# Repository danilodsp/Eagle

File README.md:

# Eagle

## Description

Some PCB projects using Eagle

## Directories

- PIC

PIC programmer PCB for development (designed in 2010).

- fonteReg

Controlled voltage source.

- fonte

Simple voltage source.

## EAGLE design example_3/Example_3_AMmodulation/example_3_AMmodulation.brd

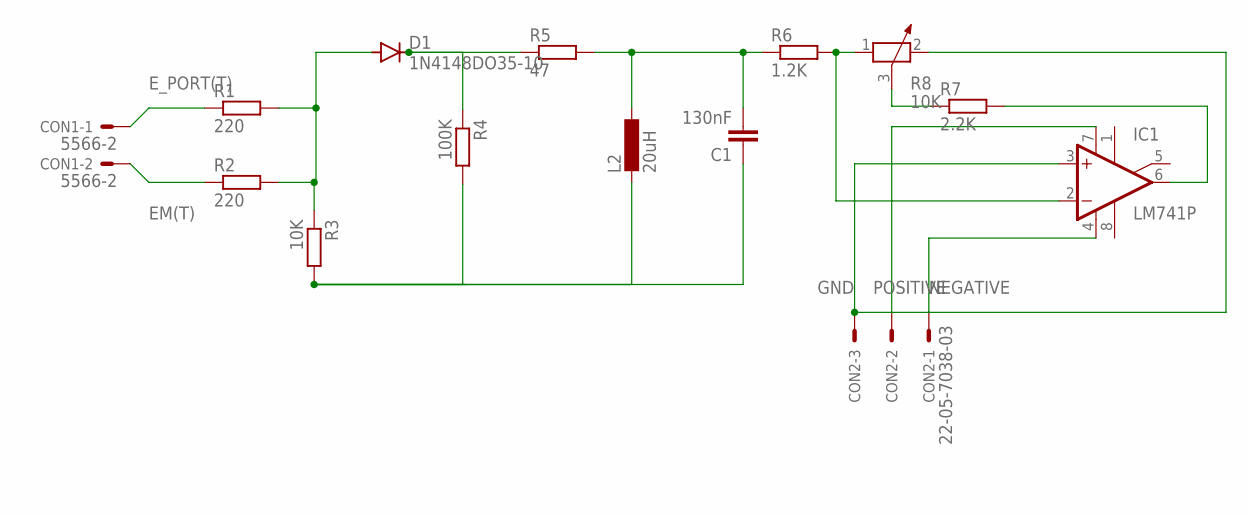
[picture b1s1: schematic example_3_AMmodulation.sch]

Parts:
C1: 130nF; C025-025X050
CON1: 5566-2
CON2: 22-05-7038-03; 7395-03
D1: 1N4148DO35-10; DO35-10
IC1: LM741P; DIL08
L2: 20uH; 0204/7
R1, R2: 220; 0204/7
R3: 10K; 0204/7
R4: 100K; 0204/7
R5: 47; 0204/7
R6: 1.2K; 0204/7
R7: 2.2K; 0204/7
R8: 10K; PT-10

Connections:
EM(T): CON1.2, R2.1
E_PORT(T): CON1.1, R1.1
GND: CON2.3, IC1.3 (+IN), R8.2
unnamed: D1.A, R1.2, R2.2, R3.1
unnamed: IC1.2 (-IN), R6.2, R8.1
unnamed: D1.C, R4.1, R5.1
unnamed: C1.2, L2.1, R5.2, R6.1
unnamed: R7.1, R8.3
unnamed: C1.1, L2.2, R3.2, R4.2
unnamed: IC1.6 (OUT), R7.2
NEGATIVE: CON2.1, IC1.4 (V-)
POSITIVE: CON2.2, IC1.7 (V+)

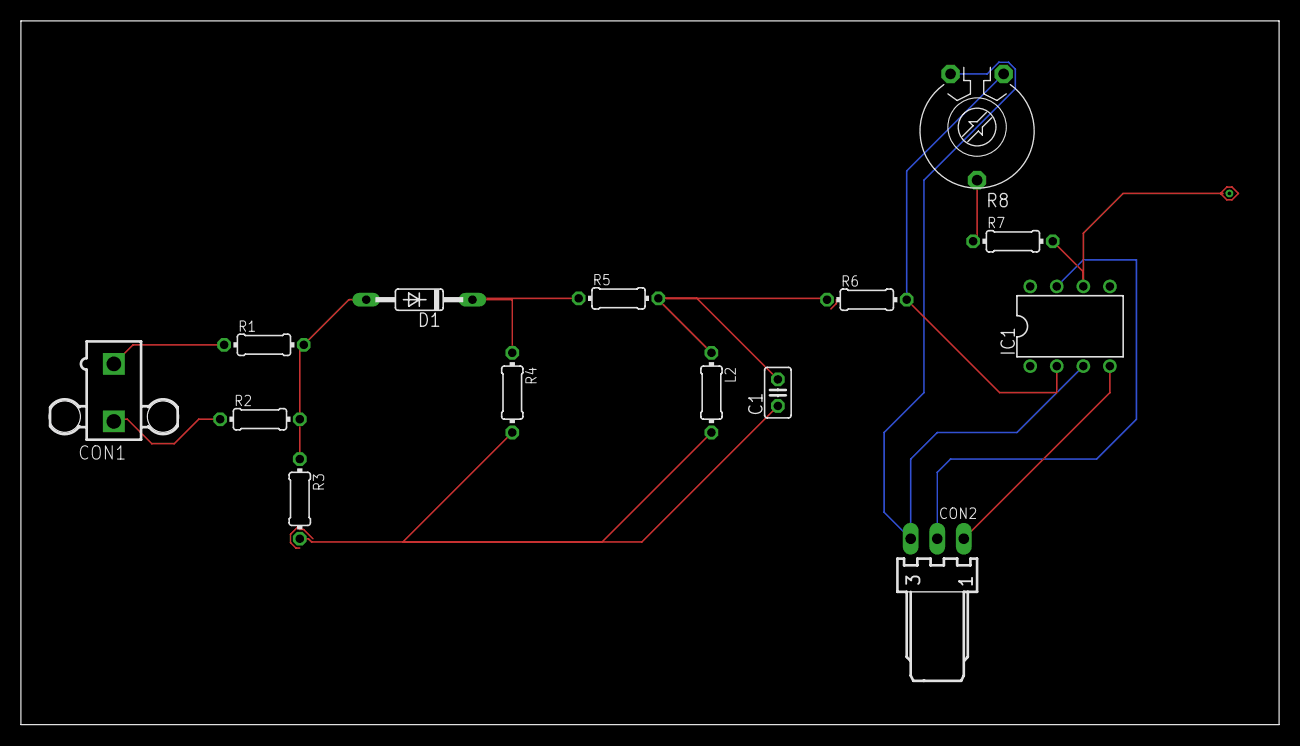
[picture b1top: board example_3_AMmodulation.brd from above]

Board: 2 copper layers, 120.3 x 67.3 mm, 14 parts (0 on the bottom side), 12 nets.

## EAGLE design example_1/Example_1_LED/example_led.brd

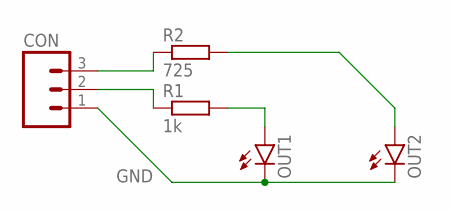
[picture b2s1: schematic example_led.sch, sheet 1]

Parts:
CON: M03; 03P
OUT1, OUT2: LED5MM
R1: 1k; 0204/7
R2: 725; 0204/7

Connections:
GND: CON.1, OUT1.K (C), OUT2.K (C)
unnamed: CON.3, R2.1
unnamed: OUT2.A, R2.2
unnamed: CON.2, R1.1
unnamed: OUT1.A, R1.2

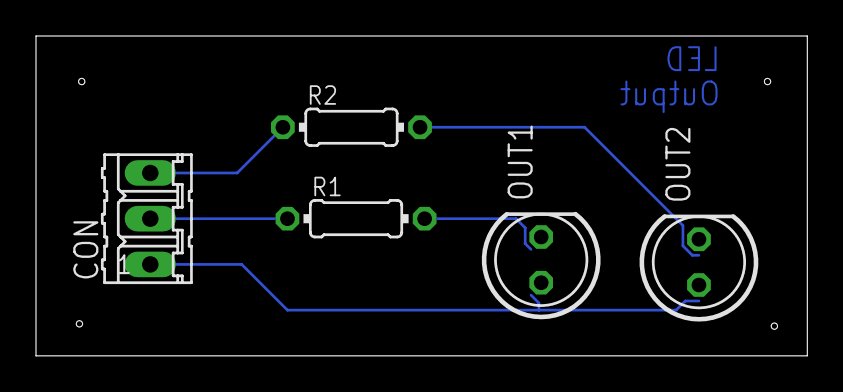
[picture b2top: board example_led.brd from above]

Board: 2 copper layers, 42.9 x 17.8 mm, 5 parts (0 on the bottom side), 5 nets.

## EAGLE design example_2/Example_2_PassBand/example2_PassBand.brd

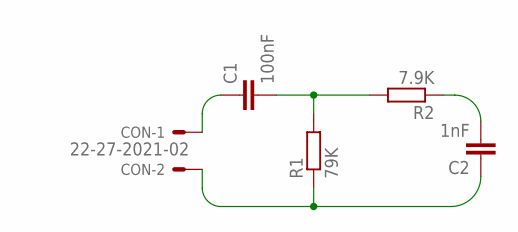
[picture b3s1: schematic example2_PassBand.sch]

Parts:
C1: 100nF; C5B2.5
C2: 1nF; C5B2.5
CON: 22-27-2021-02; 6410-02
R1: 79K; 0204/7
R2: 7.9K; 0204/7

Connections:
unnamed: C1.1, CON.1
unnamed: C1.2, R1.2, R2.2
unnamed: C2.2, R2.1
unnamed: C2.1, CON.2, R1.1

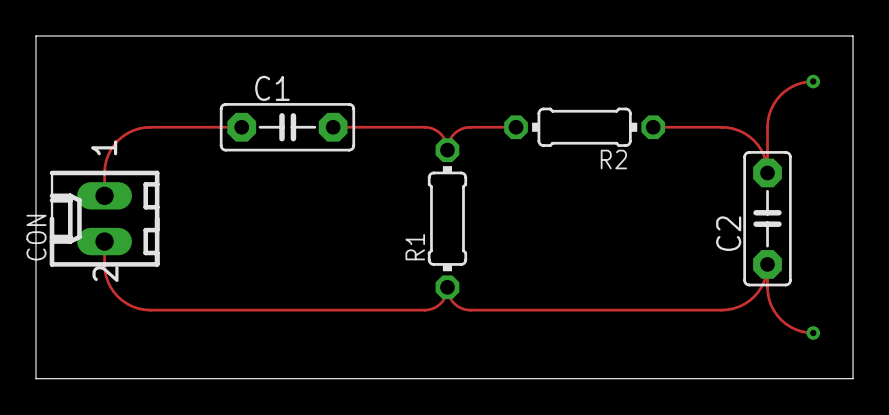
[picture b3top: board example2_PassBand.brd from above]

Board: 2 copper layers, 45.4 x 19.0 mm, 5 parts (0 on the bottom side), 4 nets.

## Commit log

2019-08-17 Added PIC programmer
2019-08-17 Updated the README
2019-08-17 Added a controlled source PCB
2019-08-17 Simple voltage source
2019-08-19 Add files via upload
    example_1 is LED and example_2 is Pass_band
2019-08-19 Add files via upload
    Example_3 - AM Modulation
